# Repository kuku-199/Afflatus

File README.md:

# Afflatus💡
           
* [**中文版本**](./README_zh.md)
## Afflatus STM32G4xx Open Development Board🚀
* This project used STM32G431 to master chip.A complete board to be made up of **Commaner**+**Expansion**
>`STM32G431CBU6` Core Board

## Commander✨📟

|Top|Bottom|
|:--:|:--:|
||

>At present core boaed onboard Flash,LED,NRST and BOOT0 keys,Reserved serial interface of LDC,Need`0.8mm wire the connection`

>Commander have used `0.8mm`BTB_2x20P，`Not connected to Expansion`Download program can use reserved SW bonding pad to connected `Cable`or`Test probe`Download program

>Commander`none the LDO and DC-DC to buck`,to the extent that core board power only give`3.3V`❗ ❗ ❗

## Expansion🔌⚡🚀

|Top|Bottom|
|:--:|:--:|
||

* 1 USB support PD
* 1 USART to USB port
* 1 IMU(BMI270)
* 1 40P header 

>Expansion have one`CP2102`USB can be connected for serial communication.STM32G431CBU6 support `UCPD`so the USB plug support PD and have one DC-DC buck module⚡

>Consider that newbies may be less likely to use the STM32's built-in USB hardware controls,so i reserved USB_D+ pull-up R CC1,CC2 pull-down R`0402`bonding pad,it's recommended to weld pull-down R for CC1 and CC2🔌

>Expansion the type of embedded stud is`M2x4x5.0x2.5x1.0`,BTB combined height is`5.0mm`
I/O Pin header is 2.54mm`SMT`.Optionally add baseplate for Expansion,[**Baseplate file**](./HDK/Expansion/Choice.dxf)effect maps

## Important statement ❗ ❗ ❗

*  ⚠️Please read the PCB Engineering Instructions pdf file
    - 📖[Engineering declaration](./%E5%B7%A5%E7%A8%8B%E5%A3%B0%E6%98%8E.pdf)
* 👓The whole project uses a two-layer process. If you don't have kicad installed, you can directly view Bom for welding. Gerber files are also in HDK
    - [**Commander-bom**](htmlpreview.github.io/?./HDK/Commander/bom/Commander.html)
    - [**Expansion-bom**](./HDK/Expansion/bom/Expansion.html)
* Continuous update, currently replenishing Demo.📃
* welcome to submit your questions, and I also hope you can submit your own updates to the project📡
* I E-mail**2981263629@qq.com**,if you have questions or new idea can send an email to me⌨
* ❗ ❗ ❗ BUG of IO silk-screen in early stage versions,do not affect usage.(Partial left-right reverse).It has now been repaired.❗ ❗ ❗

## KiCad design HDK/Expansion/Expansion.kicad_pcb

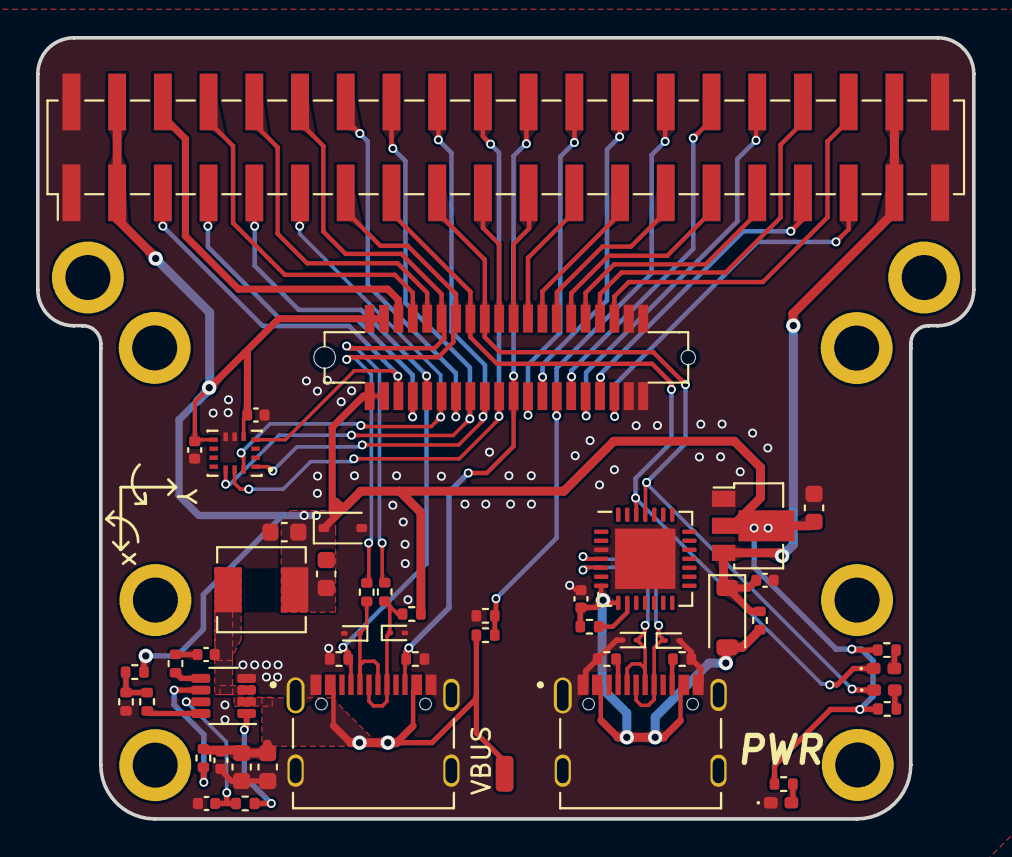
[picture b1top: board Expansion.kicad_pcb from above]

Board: 2 copper layers, 52.0 x 43.4 mm, 53 parts (1 on the bottom side), 55 nets.

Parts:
C1, C6, C7, C9, C10: 100nF; C_0402_1005Metric
C2, C3, C14: 22uF; C_0603_1608Metric
C4, C5: 10uF; C_0603_1608Metric
C8: 1uF; C_0402_1005Metric
C13: 10uF; C_0402_1005Metric
D1: LESD3Z5.0CMT1G; D_SOD-323
D2, D3, D4, D5: ESD9B5.0ST5G; D_SOD-923
D6: 1N5819WS; D_SOD-123
D7: Blue; LED_0402_1005Metric_Pad0.77x0.64mm_HandSolder
D8: Yellow; LED_0402_1005Metric_Pad0.77x0.64mm_HandSolder
D9: Yllow; LED_0402_1005Metric_Pad0.77x0.64mm_HandSolder
J2: Conn_02x20_Odd_Even; PinHeader_2x20_P2.54mm_Vertical_SMD
J3: Conn_01x01_Pin; SolderWirePad_1x01_SMD_1x2mm
J4: Afflatus-outline
L1: L; L_Sunlord_MWSA0402S
R1, R20, R21: 22R; R_0402_1005Metric
R2, R3: 100K; R_0402_1005Metric
R4: 51K; R_0402_1005Metric
R5: 41.2K; R_0402_1005Metric
R6: 13K; R_0402_1005Metric
R7, R13: 0R; R_0402_1005Metric
R8: 10K; R_0402_1005Metric
R9, R10, R11, R12: 5.1K; R_0402_1005Metric
R14, R15: 1K; R_0402_1005Metric
R18: 200K; R_0402_1005Metric
R19: 40.2K; R_0402_1005Metric
R22: 3.3K; R_0402_1005Metric
U1: TSOT-23-8
U2, U3: USB_C_16P; Typc-C-16P
U4: CP2102N-Axx-xQFN28; QFN-28-1EP_5x5mm_P0.5mm_EP3.35x3.35mm
U5: BMI270; XDCR_BMI270
U6: AMS1117; SOT-89-3
j1: BTB_0.8_2X20P_M
kibuzzard-63E5B3C4: G***; kibuzzard-63E5B3C4

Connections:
3V3: C2.2, C3.2, C9.2, C10.2, C14.1, D1.1 (A1), J2.3, J2.4, L1.2, R5.2, R7.2, R14.1, R15.1, R22.1, U5.5 (VDDIO), U5.8 (VDD), U6.2 (VO), j1.1, j1.2, j1.3, j1.4
+5V: C13.1, D6.1 (K), J2.37, J2.38, R13.1, U6.3 (VI)
/IMU.BMI270_CLK: J2.20, U5.13 (SCX), j1.19
/IMU.BMI270_CS: J2.16, U5.12 (CSB), j1.15
/IMU.BMI270_EXIT: J2.5, U5.4 (INT1), j1.5
/IMU.BMI270_MISO: J2.18, U5.1 (SDO), j1.17
/IMU.BMI270_MOSI: J2.11, U5.14 (SDX), j1.11
/MCU.USART3_RX: D8.1 (K), J2.17, U4.25 (RXD), j1.18
/MCU.USART3_TX: D7.1 (K), J2.15, U4.26 (TXD), j1.16
/MCU.USB_CC1: J2.9, R11.1, U3.A5 (CC1), j1.9
/MCU.USB_CC2: J2.22, R12.1, U3.B5 (CC2), j1.21
/MCU.USB_DN: D3.1 (A1), R20.1, U3.A7 (D-), U3.B7 (D-)
/MCU.USB_DP: D5.1 (A1), R7.1, R21.1, U3.A6 (D+), U3.B6 (D+)
/PA0: J2.26, j1.25
/PA2: J2.30, j1.30
/PA3: J2.32, j1.32
/PA4: J2.33, j1.34
/PA5: J2.35, j1.36
/PA6: J2.36, j1.35
/PA7: J2.34, j1.33
/PA8: J2.19, j1.20
/PA15: J2.14, j1.13
/PB0: J2.31, j1.31
/PB1: J2.29, j1.29
/PB2: J2.27, j1.28
/PB7: J2.7, j1.7
/PB10: J2.25, j1.26
/PB11: J2.23, j1.24
/PC6: J2.21, j1.22
/PC13: J2.24, j1.23
/SWCLK-L: J2.8, j1.8
/SWDIO-L: J2.10, j1.10
/TYPE-C/USART_USB_CC1: R9.1, U2.A5 (CC1)
/TYPE-C/USART_USB_CC2: R10.1, U2.B5 (CC2)
/TYPE-C/USART_USB_DN: D2.1 (A1), U2.A7 (D-), U2.B7 (D-), U4.5 (D-)
/TYPE-C/USART_USB_DP: D4.1 (A1), U2.A6 (D+), U2.B6 (D+), U4.4 (D+)
/VBAT_Pin: J2.6, j1.6
ADC_VBUS: J2.28, R18.2, R19.1, j1.27
GND: C2.1, C3.1, C4.2, C5.2, C6.2, C7.2, C8.1, C9.1, C10.1, C13.2, C14.2, D1.2 (A2), D2.2 (A2), D3.2 (A2), D4.2 (A2), D5.2 (A2), D9.1 (K), J2.1, J2.2, J2.39, J2.40, R6.2, R9.2, R10.2, R11.2, R12.2, R19.2, U1.4 (GND), U2.A1 (GND), U2.A12 (GND), U2.B1 (GND), U2.B12 (GND), U2.S1 (_), U2.S2 (_), U2.S3 (_), U2.S4 (_), U3.A1 (GND), U3.A12 (GND), U3.B1 (GND), U3.B12 (GND), U3.S1 (_), U3.S2 (_), U3.S3 (_), U3.S4 (_), U4.3 (GND), U4.29 (GND), U5.6 (GNDIO), U5.7 (GND), U6.1 (ADJ), j1.37, j1.38, j1.39, j1.40
unnamed: C1.1, R1.2
unnamed: D7.2 (A), R14.2
unnamed: D8.2 (A), R15.2
unnamed: D9.2 (A), R22.2
unnamed: R4.2, R5.1, R6.1
unnamed: R1.1, U1.5 (BST)
unnamed: R2.2, U1.6 (EN/SYNC)
unnamed: R4.1, U1.8 (FB)
unnamed: R3.1, U1.1 (PG)
unnamed: C1.2, L1.1, U1.3 (SW)
unnamed: C7.1, R3.2, U1.7 (VCC)
unnamed: R8.2, U4.9 (~RST)
USB_DN: J2.13, R20.2, j1.14
USB_DP: J2.12, R21.2, j1.12
VBUS: C8.2, D6.2 (A), R8.1, R13.2, U2.A4 (VBUS), U2.A9 (VBUS), U2.B4 (VBUS), U2.B9 (VBUS), U4.7 (VREGIN), U4.8 (VBUS)
VBUS1: C4.1, C5.1, C6.1, J3.1, R2.1, R18.1, U1.2 (IN), U3.A4 (VBUS), U3.A9 (VBUS), U3.B4 (VBUS), U3.B9 (VBUS)

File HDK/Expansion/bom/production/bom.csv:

Designator,Footprint,Quantity,Value,LCSC Part #
"C1, C10, C6, C7, C9",0402,5,100nF,
C13,0402,1,10uF,
"C14, C2, C3",0603,3,22uF,
"C4, C5",0603,2,10uF,
C8,0402,1,1uF,
D1,D_SOD-323,1,LESD3Z5.0CMT1G,
"D2, D3, D4, D5",D_SOD-923,4,ESD9B5.0ST5G,
D6,D_SOD-123,1,1N5819WS,
D7,0402,1,Blue,
D8,0402,1,Yellow,
D9,0402,1,Yllow,
J2,PinHeader_2x20_P2.54mm_Vertical_SMD,1,Conn_02x20_Odd_Even,
J3,SolderWirePad_1x01_SMD_1x2mm,1,Conn_01x01_Pin,
J4,Afflatus-outline,1,~,
L1,L_Sunlord_MWSA0402S,1,L,
"R1, R20, R21",0402,3,22R,
"R10, R11, R12, R9",0402,4,5.1K,
"R13, R7",0402,2,0R,
"R14, R15",0402,2,1K,
R18,0402,1,200K,
R19,0402,1,40.2K,
"R2, R3",0402,2,100K,
R22,0402,1,3.3K,
R4,0402,1,51K,
R5,0402,1,41.2K,
R6,0402,1,13K,
R8,0402,1,10K,
U1,TSOT-23-8,1,~,
"U2, U3",Typc-C-16P,2,USB_C_16P,
U4,QFN-28-1EP_5x5mm_P0.5mm_EP3.35x3.35mm,1,CP2102N-Axx-xQFN28,
U5,XDCR_BMI270,1,BMI270,
U6,SOT-89-3,1,AMS1117,
j1,BTB_0.8_2X20P_M,1,~,

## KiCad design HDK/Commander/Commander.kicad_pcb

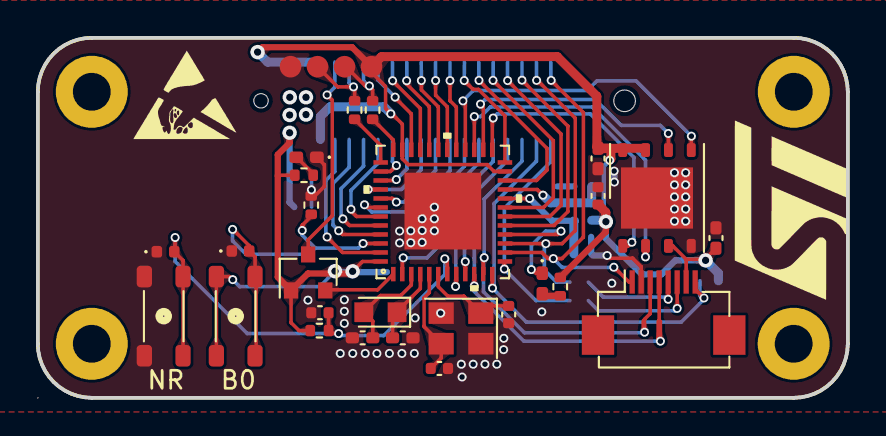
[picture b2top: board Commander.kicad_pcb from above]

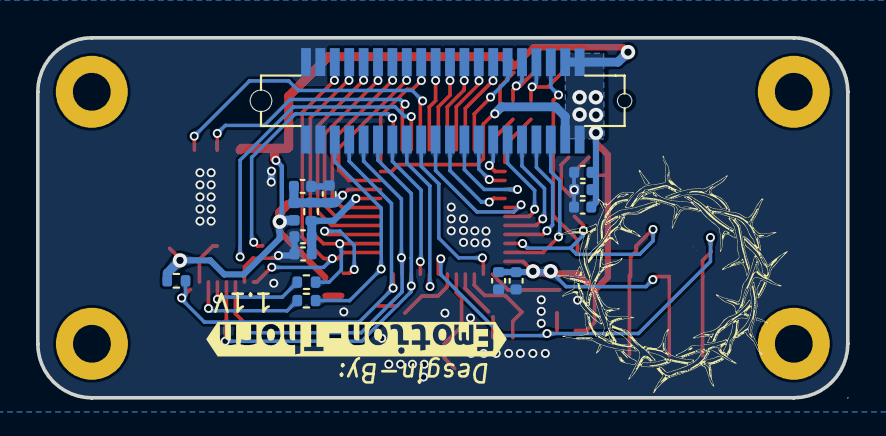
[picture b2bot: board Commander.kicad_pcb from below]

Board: 2 copper layers, 45.0 x 20.0 mm, 44 parts (16 on the bottom side), 54 nets.

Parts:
C1, C3: 1uF; C_0402_1005Metric
C2, C5, C6, C7, C8, C9, C11: 100nF; C_0402_1005Metric
C4: 10nF; C_0402_1005Metric
C10: 4.7uf; C_0402_1005Metric
C12, C13: 15pF; C_0402_1005Metric
C14, C15: 15pF; C_0402_1005Metric_Pad0.74x0.62mm_HandSolder
C16, C17: 100nF; C_0402_1005Metric_Pad0.74x0.62mm_HandSolder
D1: BAT54C; SOT-23
D2, D3: AZ5725-01F-P; D_0402_1005Metric
D6: Purple; LED_0402_1005Metric_Pad0.77x0.64mm_HandSolder
D7: White; LED_0402_1005Metric_Pad0.77x0.64mm_HandSolder
FB1: 1K 100M; L_0402_1005Metric
J1: SWD; Test_Dot
J3: FPC0.5-SMT-8; Hirose_FH12-8S-0.5SH_1x08-1MP_P0.50mm_Horizontal
J4: J
R1: 0R; R_0402_1005Metric
R2, R3: 10K; R_0402_1005Metric
R4, R5, R11, R12: 22R; R_0402_1005Metric
R10, R13: 1K; R_0402_1005Metric
R14: 100K; R_0402_1005Metric
SW1: NRST; SW_4P_3x4x2.5mm
SW2: BOOT0; SW_4P_3x4x2.5mm
U1: STM32G431CBU6
U3: W25Q128JVS; WSON-8-1EP_6x5mm_P1.27mm_EP3.4x4mm
Y1: 8M; Crystal_SMD_3225-4Pin_3.2x2.5mm
Y2: 32.768K; Crystal_SMD_2012-2Pin_2.0x1.2mm_HandSoldering
j2: BTB_0.8_2X20P_F
kibuzzard-63E5B3C4: G***; kibuzzard-63E5B3C4

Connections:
+3V3: C5.1, C6.1, C7.1, C8.1, C9.1, C10.1, C16.1, C17.1, D1.1, FB1.1, J1.4, J3.7, R2.1, R10.1, R13.1, R14.1, SW2.1, SW2.2, U1.23 (VDD), U1.35 (VDD), U1.48 (VDD), U3.3 (IO2), U3.7 (IO3), U3.8 (VCC), j2.37, j2.38, j2.39, j2.40
/BOOT0: D3.2 (A2), R3.2, SW2.3, SW2.4, U1.46 (PB8-BOOT0)
/LCD.BKControl: J3.1, U1.14 (PA6), j2.6
/LCD.CS: J3.8, R14.2, U1.12 (PA4), j2.7
/LCD.D/C: J3.4, U1.10 (PA2), j2.11
/LCD.SCL: R12.1, U1.13 (PA5), j2.5
/LCD.SDA: R11.1, U1.15 (PA7), j2.8
/LCD.~RES: J3.3, U1.11 (PA3), j2.9
/NRST: C11.1, D2.2 (A2), R2.2, SW1.3, SW1.4, U1.7 (PG10-NRST)
/OSC_32_IN: C14.1, U1.3 (PC14-OSC32_IN), Y2.2
/OSC_32_OUT: C15.1, U1.4 (PC15-OSC32_OUT), Y2.1
/OSC_IN: C12.1, U1.5 (PF0-OSC_IN), Y1.3
/OSC_OUT: C13.1, U1.6 (PF1-OSC_OUT), Y1.1
/PA0: U1.8 (PA0), j2.15
/PA1: U1.9 (PA1), j2.13
/PA8: U1.30 (PA8), j2.22
/PA9: U1.31 (PA9), j2.24
/PA10: U1.32 (PA10), j2.26
/PA11: U1.33 (PA11), j2.28
/PA12: U1.34 (PA12), j2.29
/PA15: U1.38 (PA15), j2.27
/PB0: U1.17 (PB0), j2.10
/PB1: U1.18 (PB1), j2.12
/PB2: U1.19 (PB2), j2.14
/PB3: U1.41 (PB3), j2.21
/PB4: U1.42 (PB4), j2.19
/PB5: U1.43 (PB5), j2.30
/PB6: U1.44 (PB6), j2.32
/PB7: U1.45 (PB7), j2.34
/PB9: U1.47 (PB9), j2.36
/PB10: U1.22 (PB10), j2.16
/PB11: U1.24 (PB11), j2.18
/PC4: D6.1 (K), U1.16 (PC4)
/PC6: U1.29 (PC6), j2.20
/PC10: U1.39 (PC10), j2.25
/PC11: U1.40 (PC11), j2.23
/PC13: U1.2 (PC13), j2.17
/SPI2.CLK: U1.26 (PB13), U3.6 (CLK)
/SPI2.CS: U1.25 (PB12), U3.1 (~CS)
/SPI2.MISO: U1.27 (PB14), U3.2 (DO(IO1))
/SPI2.MOSI: U1.28 (PB15), U3.5 (DI(IO0))
/SWCLK: R5.1, U1.37 (PA14)
/SWCLK-L: J1.2, R5.2, j2.33
/SWDIO: R4.1, U1.36 (PA13)
/SWDIO-L: J1.3, R4.2, j2.31
/VBAT+: D1.2, U1.1 (VBAT)
/VBAT_Pin: D1.3, j2.35
GND: C1.2, C2.2, C3.1, C4.1, C5.2, C6.2, C7.2, C8.2, C9.2, C10.2, C11.2, C12.2, C13.2, C14.2, C15.2, C16.2, C17.2, D2.1 (A1), D3.1 (A1), D7.1 (K), J1.1, J3.2, R3.1, SW1.1, SW1.2, U1.49 (EPAD), U3.4 (GND), Y1.2, Y1.4, j2.1, j2.2, j2.3, j2.4
unnamed: D6.2 (A), R10.2
unnamed: D7.2 (A), R13.2
unnamed: J3.5, R11.2
unnamed: J3.6, R12.2
unnamed: C3.2, C4.2, FB1.2, R1.1, U1.21 (VDDA)
unnamed: C1.1, C2.1, R1.2, U1.20 (VREF+)

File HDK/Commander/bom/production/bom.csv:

Designator,Footprint,Quantity,Value,LCSC Part #
"C1, C3",0402,2,1uF,
C10,0402,1,4.7uf,
"C11, C16, C17, C2, C5, C6, C7, C8, C9",0402,9,100nF,
"C12, C13, C14, C15",0402,4,15pF,
C4,0402,1,10nF,
D1,SOT-23,1,BAT54C,
"D2, D3",0402,2,AZ5725-01F-P ,
D6,0402,1,Purple,
D7,0402,1,White,
FB1,0402,1,1K 100M,
J1,Test_Dot,1,SWD,
J3,Hirose_FH12-8S-0.5SH_1x08-1MP_P0.50mm_Horizontal,1,FPC0.5-SMT-8,
J4,J,1,~,
R1,0402,1,0R,
"R10, R13",0402,2,1K,
"R11, R12, R4, R5",0402,4,22R,
R14,0402,1,100K,
"R2, R3",0402,2,10K,
SW1,SW_4P_3x4x2.5mm,1,NRST,
SW2,SW_4P_3x4x2.5mm,1,BOOT0,
U1,STM32G431CBU6,1,STM32G431CBU6,
U3,WSON-8-1EP_6x5mm_P1.27mm_EP3.4x4mm,1,W25Q128JVS,
Y1,Crystal_SMD_3225-4Pin_3.2x2.5mm,1,8M,
Y2,Crystal_SMD_2012-2Pin_2.0x1.2mm_HandSoldering,1,32.768K,
j2,BTB_0.8_2X20P_F,1,~,

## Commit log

2023-04-19 ReadMe
2023-04-19 Importance
2023-04-19 Hardware Development Kit
2023-04-19 Software Development Kit
2023-04-20 Updata Readme
2023-04-20 Readme_zh
2023-05-03 add USB_VPC_Example
2023-05-03 add Test File for CDC Speed
2023-05-03 Add ReadME for USB
2023-05-03 Updata Test
2023-05-06 Add Demo
2023-05-06 Updata Help Document
2023-05-06 Updata Design-File
2023-05-06 Updata Design-Flie
2023-05-06 Updata Readme_ZH
2023-05-07 Important
2023-05-07 Create CNAME
2023-05-07 Update CNAME
2023-05-15 amend silk-screen
2023-05-15 Add ignore mac files
2023-05-15 Add Demo of USB
2023-05-15 Updata Test files
2023-05-19 Add ADC_Demo
2023-05-19 Add Flash_Demo
2023-05-23 Add WS2812_Demo
2023-05-23 Updata Doc
2023-05-23 Add WS2812 HDK
2023-05-23 Updata Images_Demo
2023-07-04 Update Commander
2025-01-30 Add STM32G4XX for Afflatus

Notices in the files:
parts and their libraries:
Copyright 2021 Accelerated Designs. All rights reserved.
